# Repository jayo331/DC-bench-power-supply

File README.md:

# Multichannel linear bench power supply

Work in progress. At the start, i planned to add a switching pre-regulator and constant current control to an all-in-one linear regulator like lm350,lm317... The advantage of this solution is that since this regulator already comes with good line/load regulation i don't have to deal with extra stabilization. The problem is that those types of regulators also come with some big limits, some can not output voltages around zero, others can not handle the high current, and others are just too expensive for what they give, in general for all of the integrated solution voltage control (using DAC and MCU) is not as simple as i initially thought. Some regulators like 317 can be tweaked to output ~0V however the output is still limited to 1.5A in the case of the 317. I want to maintain the initial goals as much as possible (~0-25V, 5A per channel, simple) however commercial integrated linear regulators will not work without modifications. At this point, the only alternatives that come to mind are: 1) Tweak cheap regulators to reach voltages below 1.25V and boost the output current by adding an external pass transistor. 2) Build discretely a linear regulator that can handle these specs. For both solutions, extensive spice simulations are required to see which one performs better in dynamic load, transient, etc., and which one offers more performance at a price.

The regulators that i considered so far (without mod):

|                 | LM317         | LM350         | MIC29752      | LT3080        | LT3083        |
| --------------- | ------------- | ------------- | ------------- | ------------- | ------------- |
| 0V Capable      | &cross;       | &cross;       | &cross;       | &check;       | &check;       |
| 25V             | &check;       | &check;       | &check;       | &check;       | &cross;       |
| >/=5A           | &cross;       | &cross;       | &check;       | &cross;       | &cross;       |
| Active/In stock | &check;       | &check;       | &check;       | &check;       | &check;       |
| Cheap?          |Very inexpensive| Affordable   | Very expensive| Affordable    | Expensive     |
| Easy to mod?    | Easy          | Easy          | Difficult     | Very easy     | Easy          |

After some simulations, i ended up considering the discrete linear topology, which shows good results even in dynamic load. The main advantages of this solution are price and flexibility, also a good side effect is that since no mysterious pre-made ic are involved it should be easy to tweak in case of future updates.

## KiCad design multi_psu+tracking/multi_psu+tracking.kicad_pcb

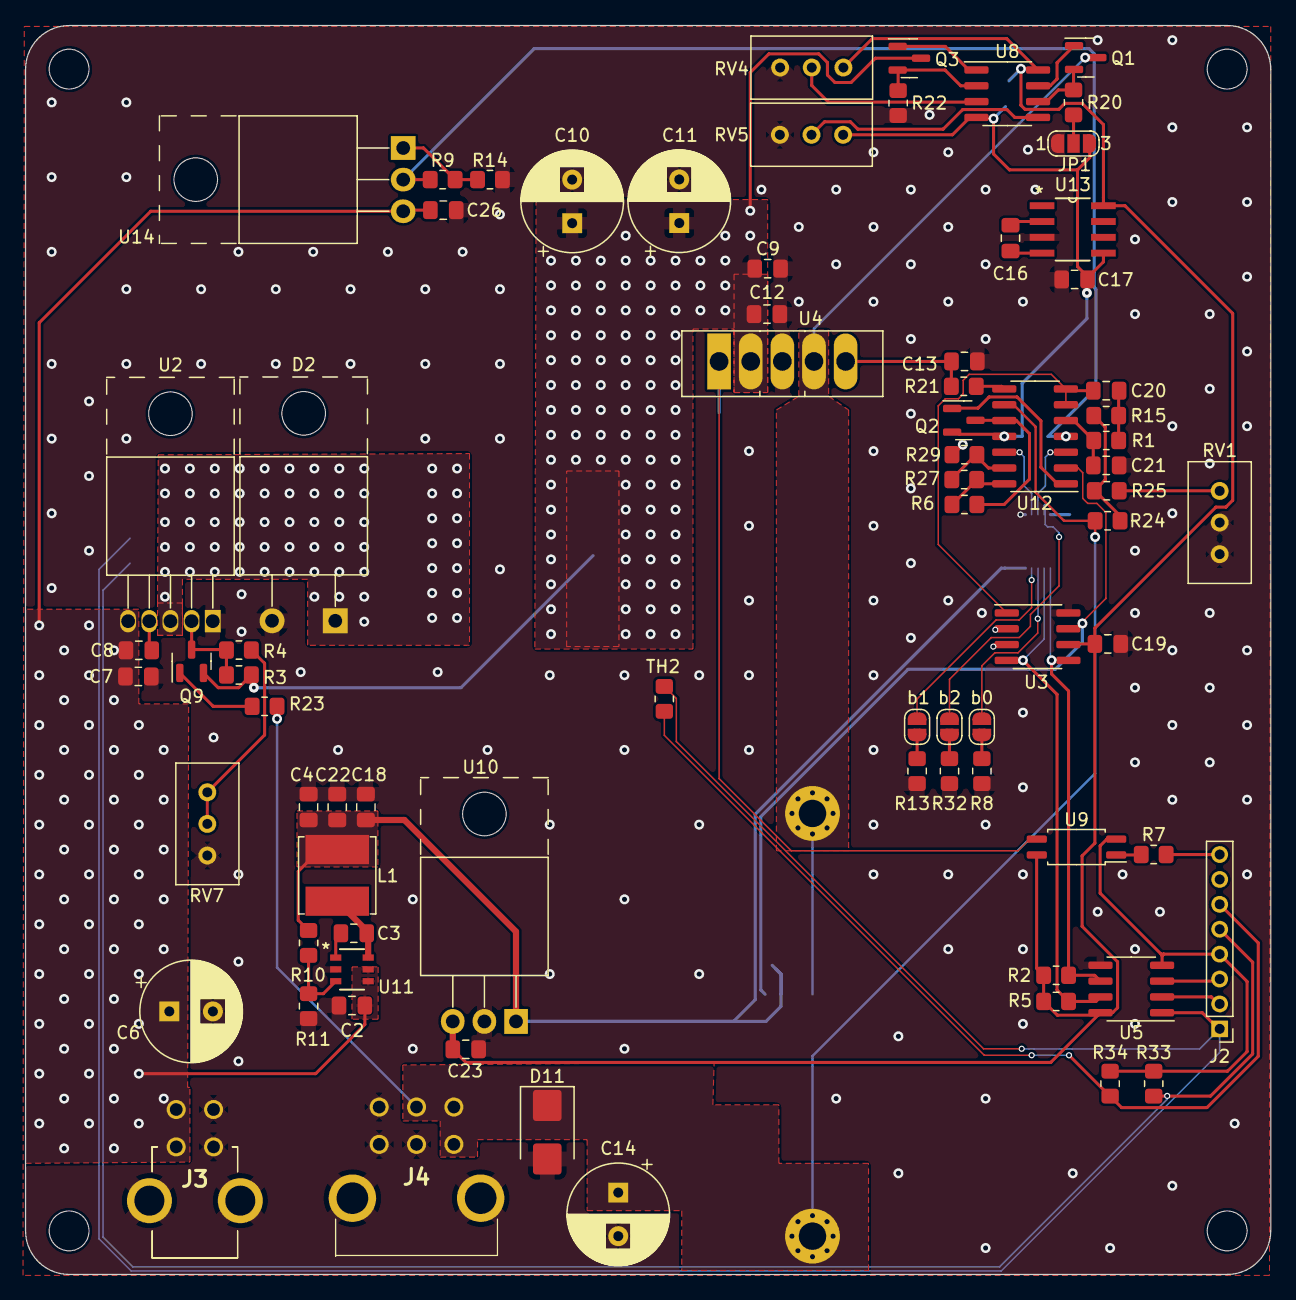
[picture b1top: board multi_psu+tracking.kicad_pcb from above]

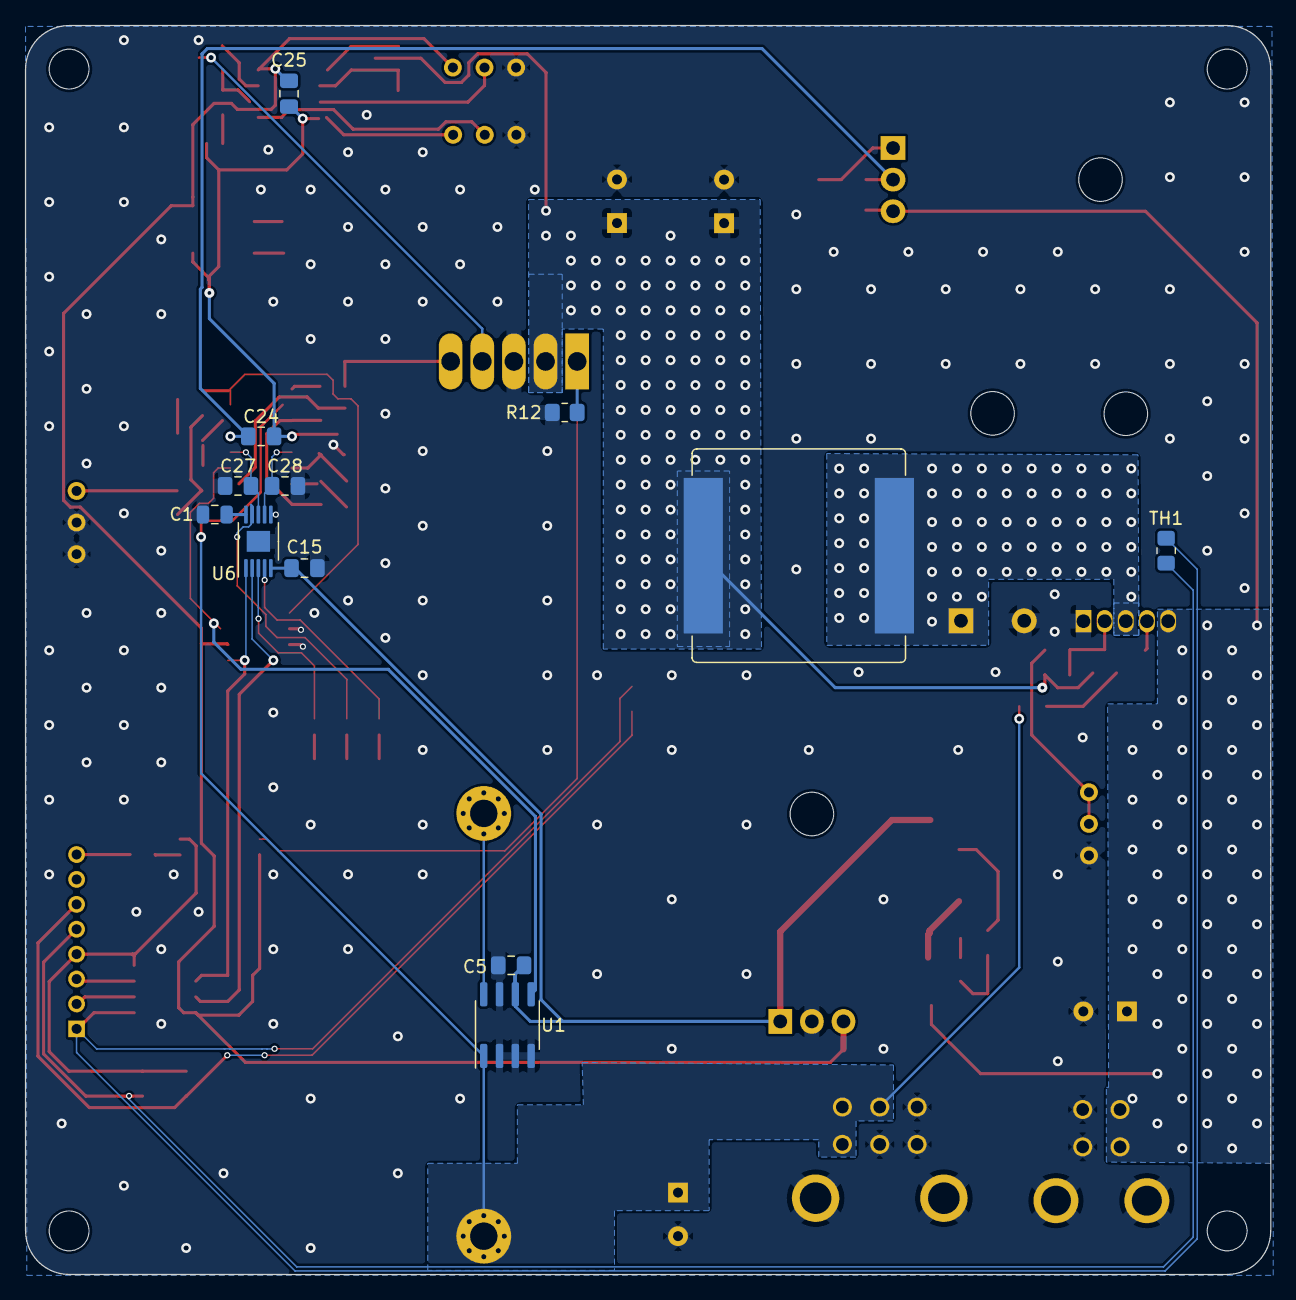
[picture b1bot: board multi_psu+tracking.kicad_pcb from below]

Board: 2 copper layers, 100.0 x 100.3 mm, 94 parts (12 on the bottom side), 59 nets.

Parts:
C1: 100n; C_0805_2012Metric
C2, C23, C26: 2.2u; C_0805_2012Metric_Pad1.18x1.45mm_HandSolder
C3, C5, C12, C15, C19, C24, C25, C27, C28: 100n; C_0805_2012Metric_Pad1.18x1.45mm_HandSolder
C4, C16, C17, C18, C22: 10u; C_0805_2012Metric_Pad1.18x1.45mm_HandSolder
C6: 470uF; CP_Radial_D8.0mm_P3.50mm
C7, C8, C9: 1uF; C_0805_2012Metric_Pad1.18x1.45mm_HandSolder
C10, C11: 1000uF; CP_Radial_D8.0mm_P3.50mm
C13: 1n; C_0805_2012Metric_Pad1.18x1.45mm_HandSolder
C14: 22u; CP_Radial_D8.0mm_P3.50mm
C20, C21: 1u; C_0805_2012Metric_Pad1.18x1.45mm_HandSolder
D2: BYV79-100; TO-220-2_Horizontal_TabUp
D11: SM6T27A; D_SMB
H1, H2, H3, H4: MountingHole; MountingHole_3.2mm_M3
H5, H6: MountingHole_Pad; MountingHole_2.2mm_M2_Pad_Via
J2: Conn_01x08_Pin; PinHeader_1x08_P2.00mm_Vertical
J3: 3-794677-4; 37946774
J4: 3-794677-6; 37946776
JP1: SolderJumper_3_Open; SolderJumper-3_P1.3mm_Open_RoundedPad1.0x1.5mm_NumberLabels
L1: 22u; L_Bourns_SRN6045TA
L2: 47uH; L_Bourns_SRP1770TA_16.9x16.9mm
Q1, Q2, Q3: 2N7002K; SOT-23
Q9: Si2319CDS; SOT-23
R1, R4, R8, R13, R15, R32: 4.7k; R_0805_2012Metric_Pad1.20x1.40mm_HandSolder
R2, R5: R; R_0805_2012Metric_Pad1.20x1.40mm_HandSolder
R3: 100k; R_0805_2012Metric_Pad1.20x1.40mm_HandSolder
R6: 2.2k; R_0805_2012Metric_Pad1.20x1.40mm_HandSolder
R7, R12: 1k; R_0805_2012Metric_Pad1.20x1.40mm_HandSolder
R9: 470; R_0805_2012Metric_Pad1.20x1.40mm_HandSolder
R10: 309k; R_0805_2012Metric_Pad1.20x1.40mm_HandSolder
R11: 22.1k; R_0805_2012Metric_Pad1.20x1.40mm_HandSolder
R14, R23, R29, R33, R34: 10k; R_0805_2012Metric_Pad1.20x1.40mm_HandSolder
R20, R22: 100; R_0805_2012Metric_Pad1.20x1.40mm_HandSolder
R21: 1; R_0805_2012Metric_Pad1.20x1.40mm_HandSolder
R24: 1M; R_0805_2012Metric_Pad1.20x1.40mm_HandSolder
R25: 200k; R_0805_2012Metric_Pad1.20x1.40mm_HandSolder
R27: 15k; R_0805_2012Metric_Pad1.20x1.40mm_HandSolder
RV1, RV4, RV5: 10k; Potentiometer_Bourns_3296W_Vertical
RV7: 500; Potentiometer_Bourns_3296W_Vertical
TH1, TH2: Thermistor_NTC; R_0805_2012Metric_Pad1.20x1.40mm_HandSolder
U1: INA241A1IDR; SOIC-8_3.9x4.9mm_P1.27mm
U2: XL4016; TO-220-5_Horizontal_TabUp
U3: MCP3422; SOIC-8_3.9x4.9mm_P1.27mm
U4: MIC29752WT; TO-247-5_Vertical
U5: ISO1640; SOIC-8_3.9x4.9mm_P1.27mm
U6: MSOP-10-1EP_3x3mm_P0.5mm_EP1.68x1.88mm
U8: LM358; SOIC-8_3.9x4.9mm_P1.27mm
U9: FODM217A; SOP-4_4.4x2.6mm_P1.27mm
U10: L7805; TO-220-3_Horizontal_TabUp
U11: AP64060QWU-7; IC6_AP64060QWU-7_DIO
U12: NCS21914; SOIC-14_3.9x8.7mm_P1.27mm
U13: TL7660CDR; D8
U14: LM317MBTG; TO-220-3_Horizontal_TabUp
b0, b1, b2: Jumper_2_Open; SolderJumper-2_P1.3mm_Open_RoundedPad1.0x1.5mm

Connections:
+5V: C19.2, C23.1, C25.1, R2.1, R5.2, RV4.1, U3.6 (Vss), U5.8 (VCC2), U8.8 (V+), U9.4, U10.3 (OUT), U13.8 (VCC)
+5VA: J2.1, TH1.1, TH2.1, U5.1 (VCC1)
+12V: C4.1, C5.2, C15.2, C18.1, C22.1, L1.2, R10.1, U1.6 (V+), U6.5 (VCC), U10.1 (IN)
+28V: C24.1, R9.1, U12.4 (V+), U14.2 (VO)
+36V: C2.1, C6.1, C7.1, C8.1, C26.1, J3.1, J3.2, U2.5 (VIN), U11.4 (EN), U11.5 (VIN), U14.3 (VI)
-5V: C17.1, C24.2, C25.2, JP1.3 (B), Q2.2 (S), RV5.3, U8.4 (V-), U12.11 (V-), U13.5 (VOUT)
ENABLE: R12.2, U4.1 (EN), U9.3
GND: C1.2, C2.2, C4.2, C5.1, C6.2, C7.2, C9.2, C10.2, C11.2, C12.2, C13.1, C14.2, C15.1, C17.2, C18.2, C19.1, C21.1, C22.2, C23.2, C26.2, C27.2, C28.2, D2.2 (A), D11.2 (A2), J3.3, J3.4, J3.MH1, J3.MH2, J4.1, J4.2, J4.3, J4.MH1, J4.MH2, JP1.1 (A), R8.2, R11.2, R12.1, R13.2, R14.2, R22.2, R29.1, R32.2, RV1.2, RV1.3, RV4.3, RV5.1, RV7.3, U1.2 (GND), U1.3 (REF2), U1.4 (GND), U1.7 (REF1), U2.1 (GND), U3.2 (CH1-), U3.3 (Vdd), U3.8 (CH2-), U4.3 (GND), U5.5 (GND2), U6.6 (GND), U6.11, U10.2 (GND), U11.2 (GND), U13.3 (GND)
GNDS: J2.4, R33.1, R34.1, U5.4 (GND1), U9.2
I_Sense: U1.5, U3.7 (CH2+), U12.2 (-)
I_ctrl: C27.1, U6.8 (VOUT2), U12.3 (+)
LIN_temp: J2.6, R34.2, TH2.2
unnamed: C20.1, R1.1, R15.2
unnamed: D2.1 (K), L2.1, U2.3 (SW)
unnamed: J2.2, U5.2 (SDA1)
unnamed: J2.3, U5.3 (SCL1)
unnamed: J2.8, R7.1
unnamed: JP1.2 (C), R20.2
unnamed: U6.9 (A2), b2.1 (A)
unnamed: R32.1, b2.2 (B)
unnamed: U6.3 (A0), b0.1 (A)
unnamed: R8.1, b0.2 (B)
unnamed: U6.4 (A1), b1.1 (A)
unnamed: R13.1, b1.2 (B)
unnamed: Q1.1 (G), U8.7
unnamed: Q1.2 (S), R20.1, U8.6 (-)
unnamed: Q2.3 (D), R6.2, U12.10 (+)
unnamed: Q2.1 (G), U12.1
unnamed: Q3.1 (G), U8.1
unnamed: Q3.2 (S), R22.1, U8.2 (-)
unnamed: Q9.3 (D), R3.2, R4.1, U2.2 (FB)
unnamed: Q9.1 (G), R23.1
unnamed: R4.2, RV7.1, RV7.2
unnamed: R7.2, U9.1
unnamed: R15.1, R24.2, R25.1
unnamed: R21.2, U12.8
unnamed: R25.2, RV1.1
unnamed: R6.1, R27.2, U12.14
unnamed: C8.2, U2.4 (VC)
unnamed: C13.2, R21.1, U4.5 (ADJ)
unnamed: C1.1, U6.10 (V5V)
unnamed: RV4.2, U8.3 (+)
unnamed: RV5.2, U8.5 (+)
unnamed: C3.2, U11.1 (BST)
unnamed: R10.2, R11.1, U11.3 (FB)
unnamed: C3.1, L1.1, U11.6 (SW)
unnamed: C21.2, R1.2, U12.5 (+)
unnamed: R27.1, R29.2, U12.13 (-)
unnamed: C16.1, U13.2 (CAP+)
unnamed: C16.2, U13.4 (CAP-)
unnamed: R9.2, R14.1, U14.1 (ADJ)
PREREG_temp: J2.5, R33.2, TH1.2
PRE_OUT: C9.1, C10.1, C11.1, C12.1, L2.2, Q3.3 (D), Q9.2 (S), R3.1, U4.2 (VIN)
S+: H5.1, Q1.3 (D), U1.8 (+), U4.4 (VOUT)
S-: C14.1, D11.1 (A1), H6.1, J4.4, J4.5, J4.6, R23.2, R24.1, U1.1 (-), U12.9 (-)
SCL: R2.2, U3.5 (SCL), U5.6 (SCL2), U6.1 (SCK)
SDA: R5.1, U3.4 (SDA), U5.7 (SDA2), U6.2 (SDA)
V_Sense: C20.2, U3.1 (CH1+), U12.6 (-), U12.7
V_ctrl: C28.1, U6.7 (VOUT1), U12.12 (+)

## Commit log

2024-01-01 Minor design update
2024-02-18 Architecture update
2024-08-23 Updated simulation files
2025-01-17 Add linear post regulator images
2025-01-17 Create Simulation folder
2025-01-17 Create a
2025-01-17 Clenup
2025-01-17 Add Pspice simulation
